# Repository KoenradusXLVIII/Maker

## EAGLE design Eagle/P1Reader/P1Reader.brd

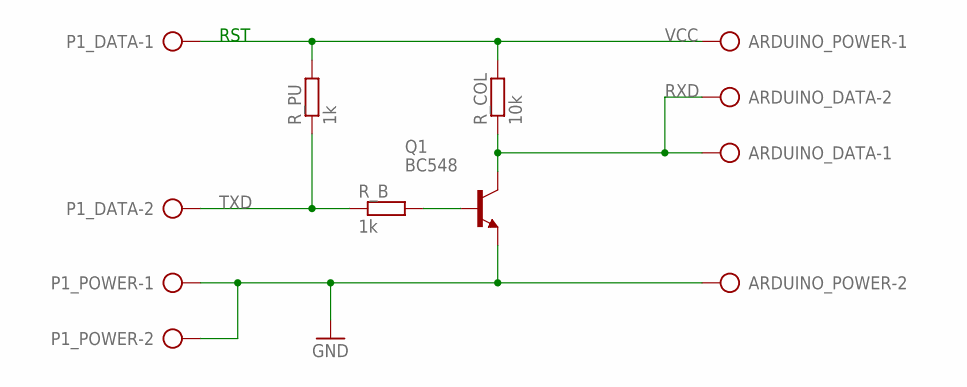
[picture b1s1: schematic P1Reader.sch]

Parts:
ARDUINO_DATA: AK500/2-H
ARDUINO_POWER: AK500/2-H
P1_DATA, P1_POWER: AK500/2-H
Q1: BC548; TO92-EBC
R_B: 1k; 0207/7
R_COL: 10k; 0207/7
R_PU: 1k; 0207/7

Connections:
GND: ARDUINO_POWER.2, P1_POWER.1, P1_POWER.2, Q1.E
unnamed: Q1.B, R_B.2
RXD: ARDUINO_DATA.1, ARDUINO_DATA.2, Q1.C, R_COL.1
TXD: P1_DATA.2, R_B.1, R_PU.1
VCC: ARDUINO_POWER.1, P1_DATA.1, R_COL.2, R_PU.2

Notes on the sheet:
RST

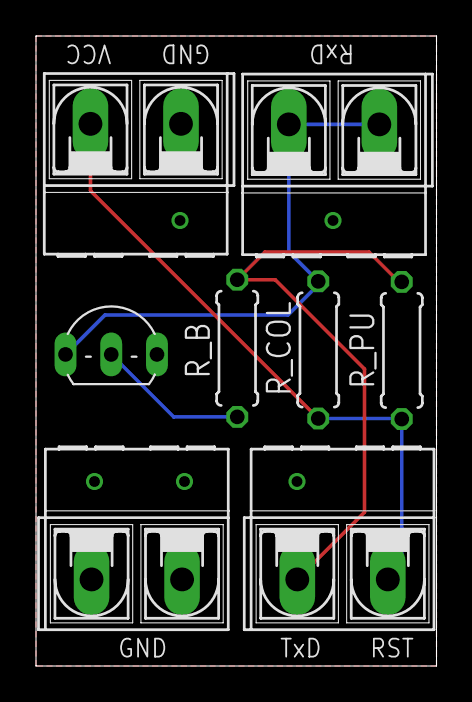
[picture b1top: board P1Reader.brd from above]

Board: 2 copper layers, 22.2 x 35.0 mm, 8 parts (0 on the bottom side), 5 nets.

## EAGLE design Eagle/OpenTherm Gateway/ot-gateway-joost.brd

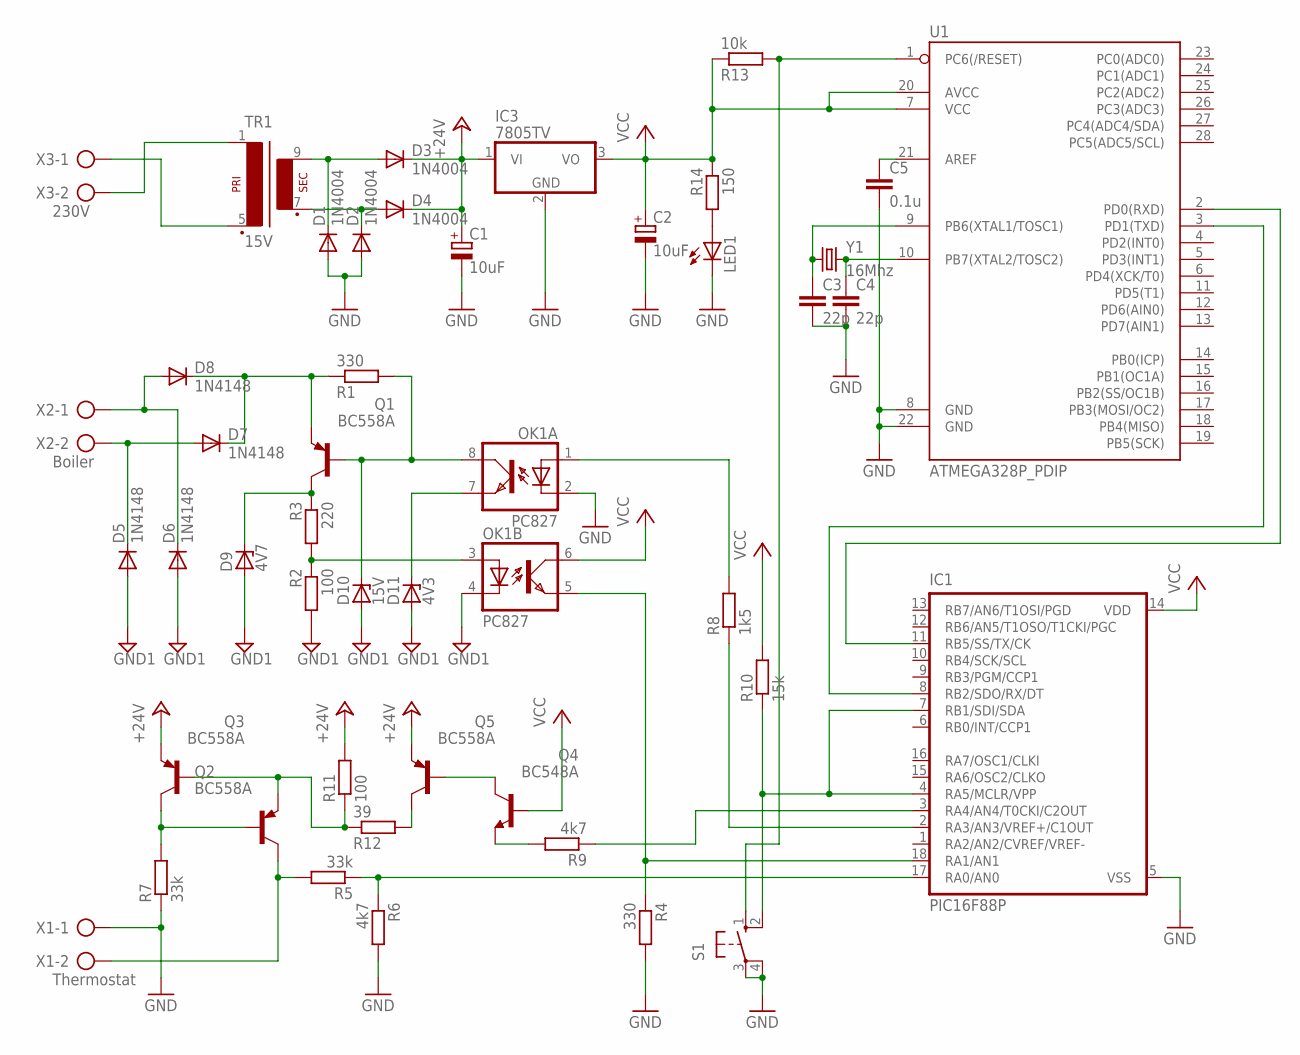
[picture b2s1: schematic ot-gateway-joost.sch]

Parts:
C1, C2: 10uF; E2,5-6
C3, C4: 22p; C025-024X044
C5: 0.1u; C025-024X044
D1, D2, D3, D4: 1N4004; DO41-10
D5, D6, D7, D8: 1N4148; DO35-10
D9: 4V7; DO41Z10
D10: 15V; DO41Z10
D11: 4V3; DO41Z10
IC1: PIC16F88P; DIL18
IC3: 7805TV; TO220V
LED1: LED3MM
OK1: PC827; DIL08
Q1, Q2, Q3, Q5: BC558A; TO92-EBC
Q4: BC548A; TO92-EBC
R1, R4: 330; 0204/7
R2, R11: 100; 0204/7
R3: 220; 0204/7
R5, R7: 33k; 0204/7
R6, R9: 4k7; 0204/7
R8: 1k5; 0204/7
R10: 15k; 0204/7
R12: 39; 0204/7
R13: 10k; 0204/7
R14: 150; 0204/7
S1: 10-XX; B3F-10XX
TR1: 15V; EI30-1
U1: ATMEGA328P_PDIP; DIL28-3
X1: Thermostat; AK500/2
X2: Boiler; AK500/2
X3: 230V; AK500/2
Y1: 16Mhz; HC49US

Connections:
+24V: C1.+, D3.C, D4.C, IC3.1 (VI), Q3.E, Q5.E, R11.2
GND: C1.-, C2.-, C3.2, C4.2, C5.2, D1.A, D2.A, IC1.5 (VSS), IC3.2 (GND), LED1.K (C), OK1.2 (C), R4.2, R6.2, R7.1, S1.3, S1.4 (P1), U1.8 (GND), U1.22 (GND), X1.1
GND1: D5.A, D6.A, D9.A, D10.A, D11.A, OK1.4 (C), R2.2
unnamed: D7.C, D8.C, Q1.E, R1.1
unnamed: Q2.B, Q3.C, R7.2
unnamed: Q2.C, R5.2, X1.2
unnamed: Q2.E, Q3.B, R11.1, R12.1
unnamed: OK1.3 (A), R2.1, R3.2
unnamed: IC1.3 (RA4/AN4/T0CKI/C2OUT), R9.1
unnamed: Q4.C, Q5.B
unnamed: D9.C, Q1.C, R3.1
unnamed: IC1.8 (RB2/SDO/RX/DT), U1.3 (PD1(TXD))
unnamed: D10.C, OK1.8 (COL), Q1.B, R1.2
unnamed: Q5.C, R12.2
unnamed: IC1.2 (RA3/AN3/VREF+/C1OUT), R8.1
unnamed: IC1.17 (RA0/AN0), R5.1, R6.1
unnamed: IC1.11 (RB5/SS/TX/CK), U1.2 (PD0(RXD))
unnamed: R13.2, S1.1 (S), U1.1 (PC6(/RESET))
unnamed: LED1.A, R14.2
unnamed: C3.1, U1.9 (PB6(XTAL1/TOSC1)), Y1.1
unnamed: C4.1, U1.10 (PB7(XTAL2/TOSC2)), Y1.2
unnamed: C5.1, U1.21 (AREF)
unnamed: D5.C, D7.A, X2.2
unnamed: D6.C, D8.A, X2.1
unnamed: D2.C, D4.A, TR1.7 (S3)
unnamed: D1.C, D3.A, TR1.9 (S4)
unnamed: TR1.5 (P2), X3.1
unnamed: IC1.18 (RA1/AN1), OK1.5 (EMIT), R4.1
unnamed: D11.C, OK1.7 (EMIT)
unnamed: IC1.4 (RA5/MCLR/VPP), IC1.7 (RB1/SDI/SDA), R10.1, S1.2 (S1)
unnamed: TR1.1, X3.2
unnamed: Q4.E, R9.2
unnamed: OK1.1 (A), R8.2
VCC: C2.+, IC1.14 (VDD), IC3.3 (VO), OK1.6 (COL), Q4.B, R10.2, R13.1, R14.1, U1.7 (VCC), U1.20 (AVCC)

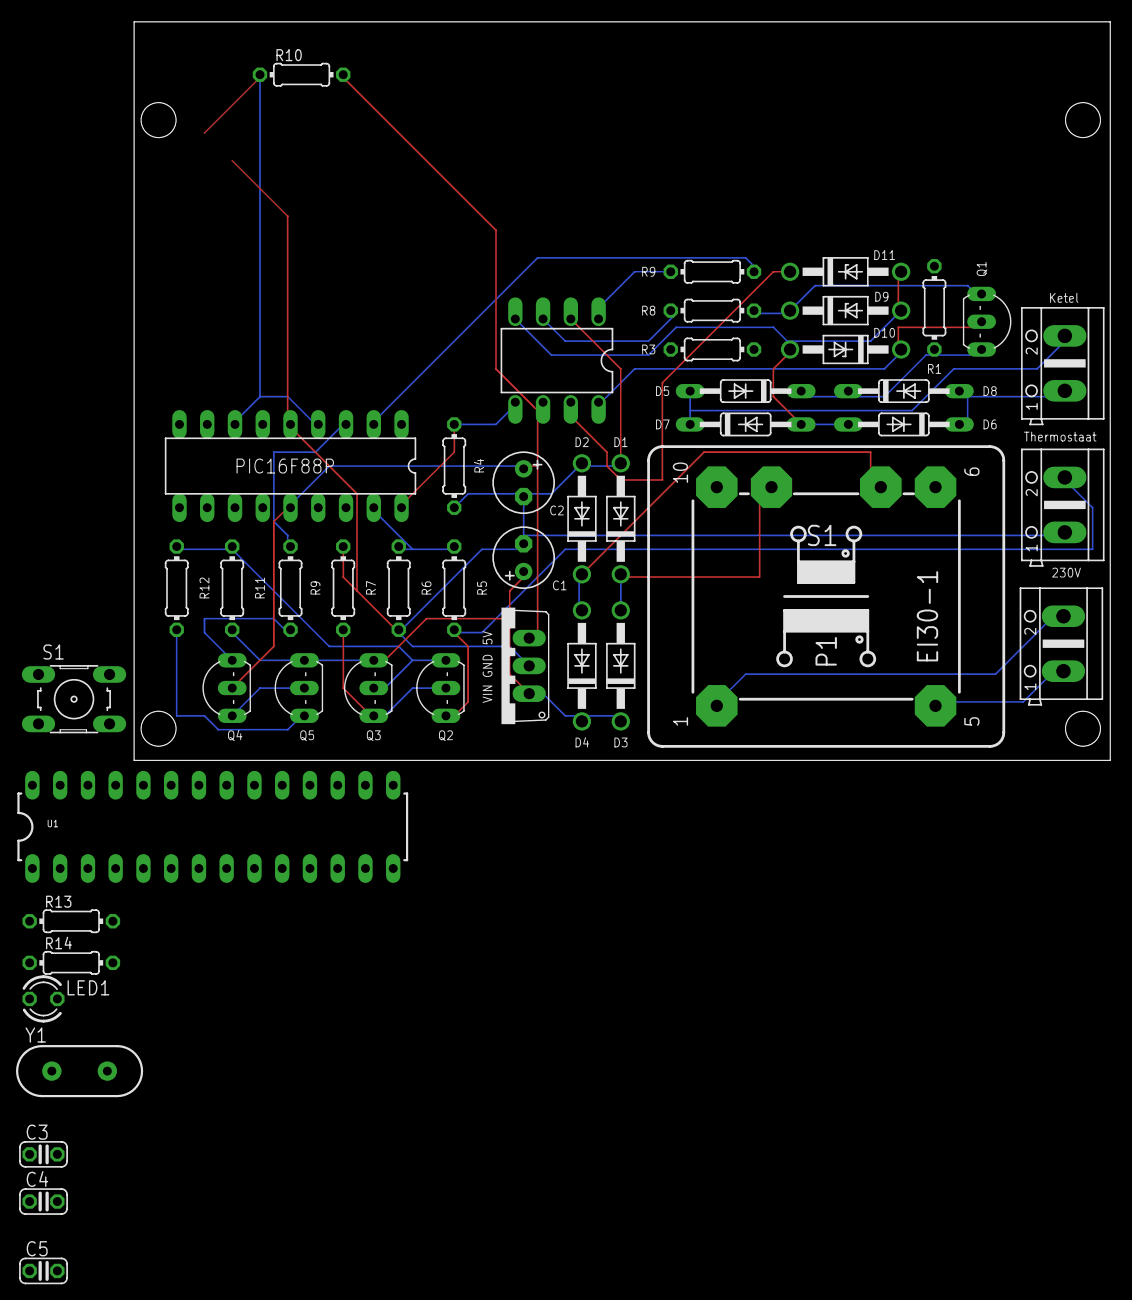
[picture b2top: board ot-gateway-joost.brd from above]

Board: 2 copper layers, 89.3 x 67.6 mm, 46 parts (0 on the bottom side), 34 nets.

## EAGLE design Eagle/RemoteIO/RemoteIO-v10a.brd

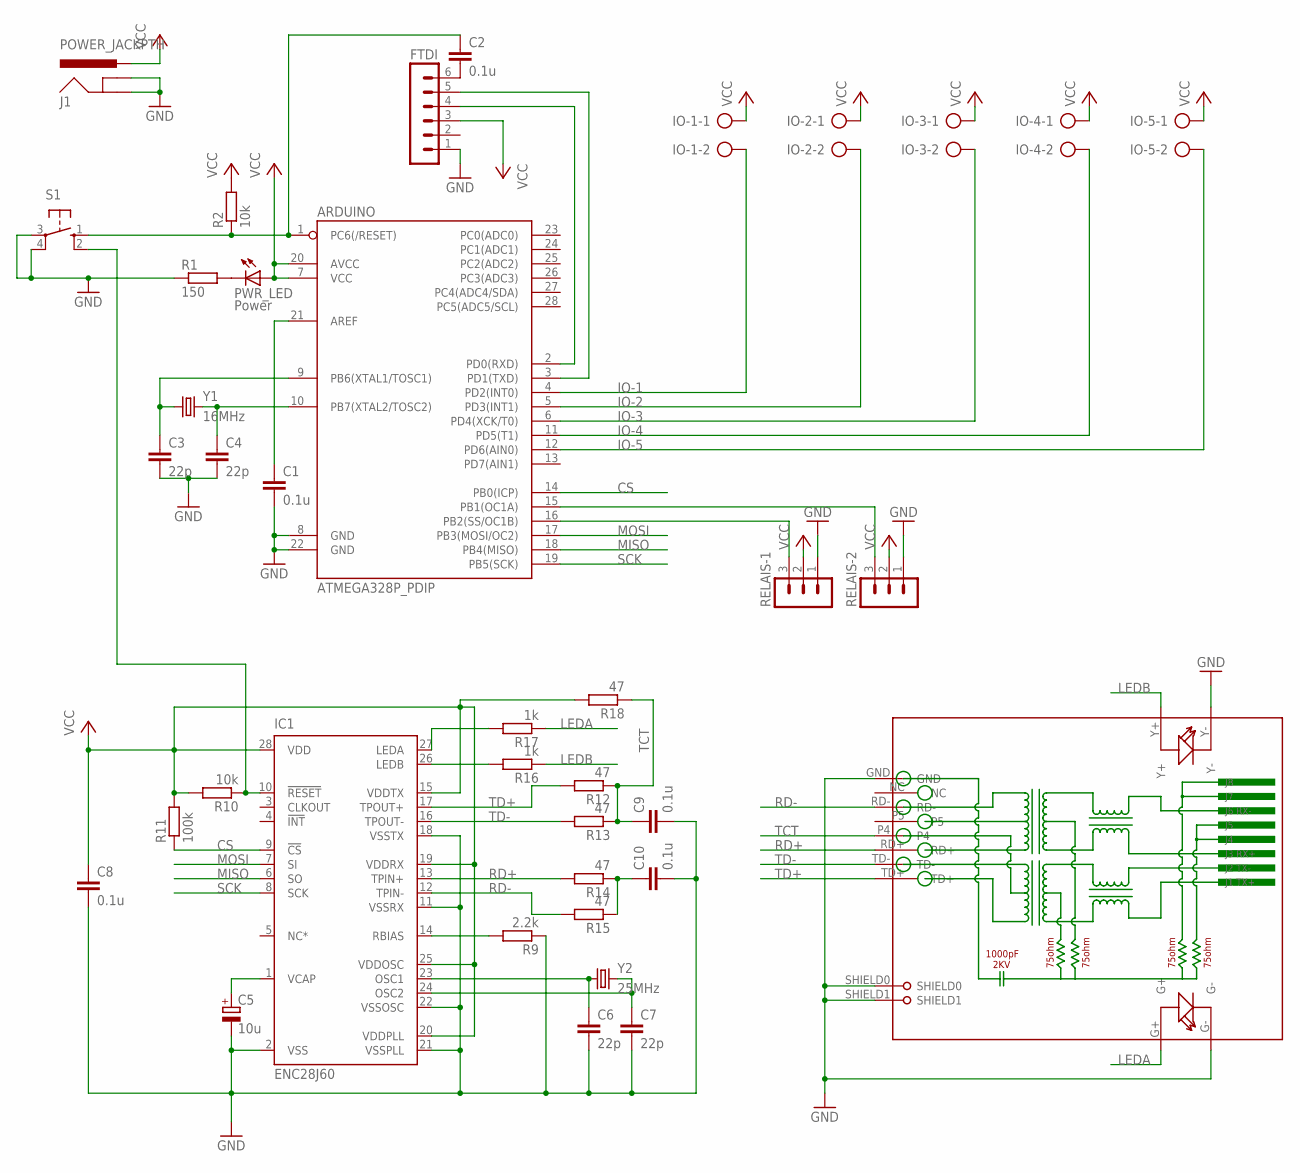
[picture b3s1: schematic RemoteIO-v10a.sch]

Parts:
ARDUINO: ATMEGA328P_PDIP; DIL28-3
C1, C2, C8, C9, C10: 0.1u; C025-024X044
C3, C4, C6, C7: 22p; C025-024X044
C5: 10u; E2,5-6
FTDI: MA06-1
IC1: ENC28J60; DIL28-3
IO-1, IO-2, IO-3, IO-4, IO-5: AK500/2
J1: POWER_JACKPTH; POWER_JACK_PTH
PWR_LED: Power; LED3MM
R1: 150; 0207/7
R2, R10: 10k; 0207/7
R9: 2.2k; 0207/7
R11: 100k; 0207/7
R12, R13, R14, R15, R18: 47; 0207/7
R16, R17: 1k; 0207/7
RELAIS-1, RELAIS-2: MA03-1
RJ1: HR911105A
S1: 10-XX; B3F-10XX
Y1: 16MHz; HC49US
Y2: 25MHz; HC49US

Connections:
CS: ARDUINO.14 (PB0(ICP)), IC1.9 (!CS), R11.1
GND: ARDUINO.8 (GND), ARDUINO.22 (GND), C1.2, C3.2, C4.2, C5.-, C6.2, C7.2, C8.2, C9.2, C10.2, FTDI.1, IC1.2 (VSS), IC1.11 (VSSRX), IC1.18 (VSSTX), IC1.21 (VSSPLL), IC1.22 (VSSOSC), J1.GND, J1.GNDBREAK, R1.1, R9.1, RELAIS-1.1, RELAIS-2.1, RJ1.G-, RJ1.GND, RJ1.SHIELD0, RJ1.SHIELD1, RJ1.Y-, S1.3, S1.4 (P1)
IO-1: ARDUINO.4 (PD2(INT0)), IO-1.2
IO-2: ARDUINO.5 (PD3(INT1)), IO-2.2
IO-3: ARDUINO.6 (PD4(XCK/T0)), IO-3.2
IO-4: ARDUINO.11 (PD5(T1)), IO-4.2
IO-5: ARDUINO.12 (PD6(AIN0)), IO-5.2
LEDA: R17.1, RJ1.G+
LEDB: R16.1, RJ1.Y+
MISO: ARDUINO.18 (PB4(MISO)), IC1.6 (SO)
MOSI: ARDUINO.17 (PB3(MOSI/OC2)), IC1.7 (SI)
unnamed: ARDUINO.1 (PC6(/RESET)), C2.1, R2.1, S1.1 (S)
unnamed: ARDUINO.9 (PB6(XTAL1/TOSC1)), C3.1, Y1.1
unnamed: ARDUINO.10 (PB7(XTAL2/TOSC2)), C4.1, Y1.2
unnamed: ARDUINO.21 (AREF), C1.1
unnamed: PWR_LED.K (C), R1.2
unnamed: IC1.14 (RBIAS), R9.2
unnamed: ARDUINO.16 (PB2(SS/OC1B)), RELAIS-1.3
unnamed: C2.2, FTDI.6
unnamed: ARDUINO.3 (PD1(TXD)), FTDI.5
unnamed: ARDUINO.2 (PD0(RXD)), FTDI.4
unnamed: C6.1, IC1.23 (OSC1), Y2.1
unnamed: IC1.26 (LEDB), R16.2
unnamed: ARDUINO.15 (PB1(OC1A)), RELAIS-2.3
unnamed: C5.+, IC1.1 (VCAP)
unnamed: C7.1, IC1.24 (OSC2), Y2.2
unnamed: C10.1, R14.1, R15.1
unnamed: IC1.27 (LEDA), R17.2
unnamed: IC1.10 (!RESET), R10.1, S1.2 (S1)
RD+: IC1.13 (TPIN+), R14.2, RJ1.RD+
RD-: IC1.12 (TPIN-), R15.2, RJ1.RD-
SCK: ARDUINO.19 (PB5(SCK)), IC1.8 (SCK)
TCT: C9.1, R12.1, R13.1, R18.1, RJ1.P4
TD+: IC1.17 (TPOUT+), R12.2, RJ1.TD+
TD-: IC1.16 (TPOUT-), R13.2, RJ1.TD-
VCC: ARDUINO.7 (VCC), ARDUINO.20 (AVCC), C8.1, FTDI.3, IC1.15 (VDDTX), IC1.19 (VDDRX), IC1.20 (VDDPLL), IC1.25 (VDDOSC), IC1.28 (VDD), IO-1.1, IO-2.1, IO-3.1, IO-4.1, IO-5.1, J1.PWR, PWR_LED.A, R2.2, R10.2, R11.2, R18.2, RELAIS-1.2, RELAIS-2.2

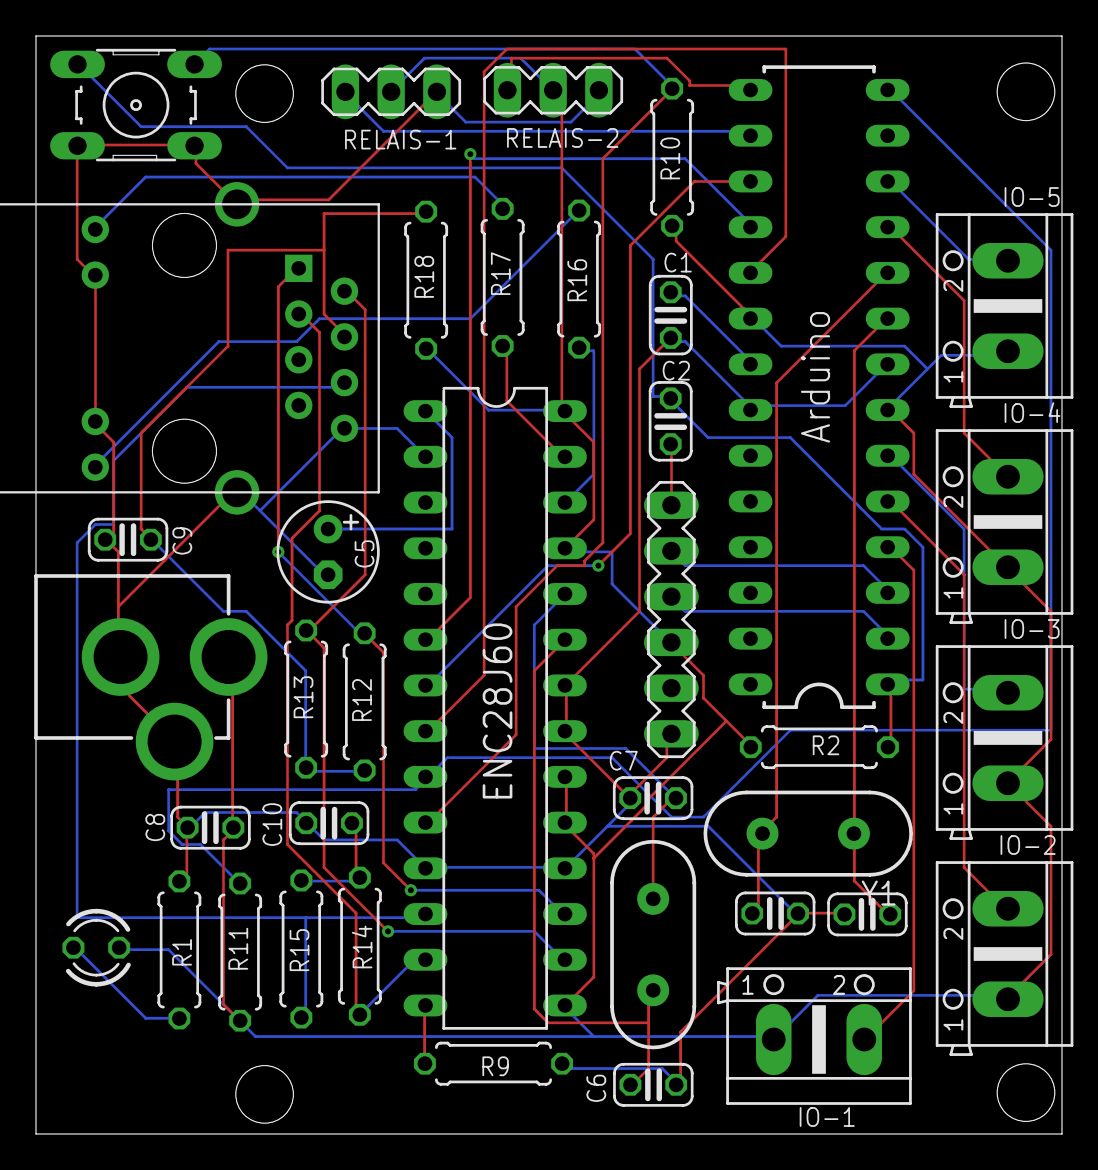
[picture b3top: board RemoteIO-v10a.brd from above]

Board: 2 copper layers, 57.0 x 61.0 mm, 38 parts (0 on the bottom side), 36 nets.

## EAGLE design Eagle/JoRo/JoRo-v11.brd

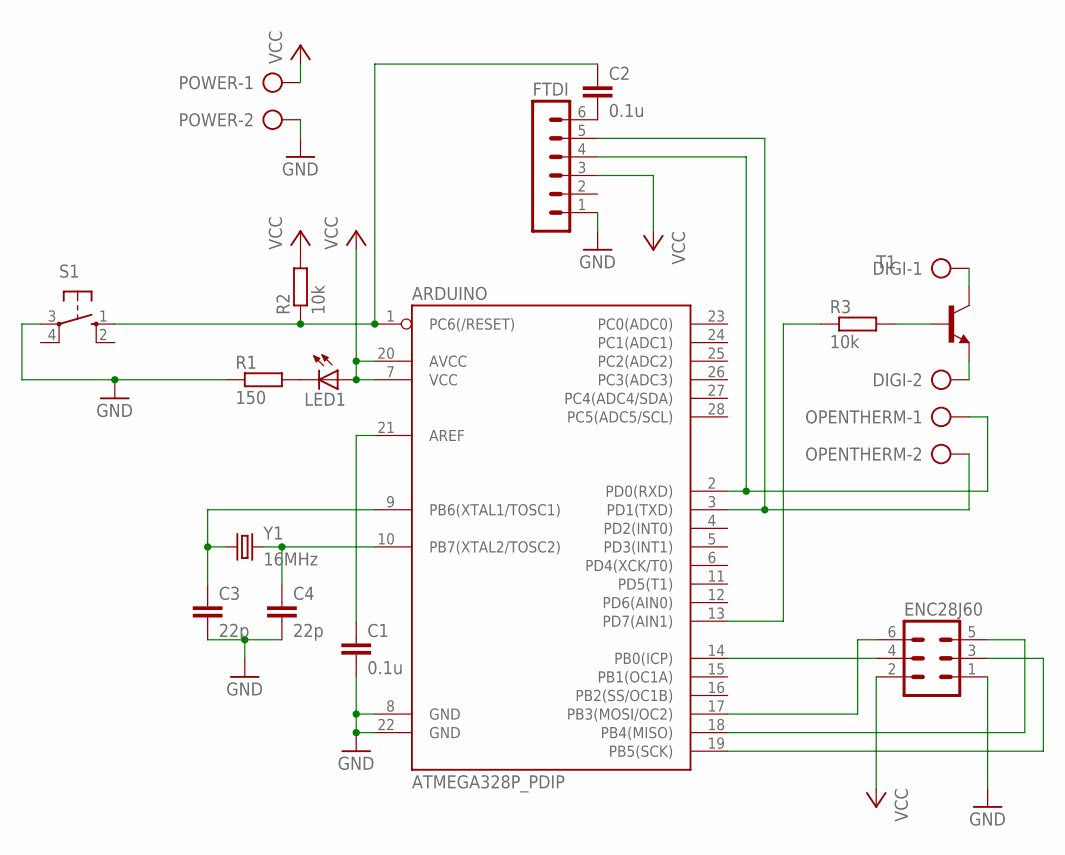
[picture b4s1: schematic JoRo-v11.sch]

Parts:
ARDUINO: ATMEGA328P_PDIP; DIL28-3
C1, C2: 0.1u; C025-024X044
C3, C4: 22p; C025-024X044
DIGI: AK500/2
ENC28J60: MA03-2
FTDI: MA06-1
LED1: LED3MM
OPENTHERM: AK500/2
POWER: AK500/2
R1: 150; 0207/7
R2, R3: 10k; 0207/7
S1: 10-XX; B3F-10XX
T1: BC548-NPN-TO92-CBE; TO92-CBE
Y1: 16MHz; HC49US

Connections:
GND: ARDUINO.8 (GND), ARDUINO.22 (GND), C1.2, C3.2, C4.2, ENC28J60.1, FTDI.1, POWER.2, R1.1, S1.3
unnamed: ARDUINO.1 (PC6(/RESET)), C2.1, R2.1, S1.1 (S)
unnamed: ARDUINO.9 (PB6(XTAL1/TOSC1)), C3.1, Y1.1
unnamed: ARDUINO.10 (PB7(XTAL2/TOSC2)), C4.1, Y1.2
unnamed: ARDUINO.21 (AREF), C1.1
unnamed: LED1.K (C), R1.2
unnamed: ARDUINO.19 (PB5(SCK)), ENC28J60.3
unnamed: C2.2, FTDI.6
unnamed: ARDUINO.3 (PD1(TXD)), FTDI.5, OPENTHERM.2
unnamed: ARDUINO.2 (PD0(RXD)), FTDI.4, OPENTHERM.1
unnamed: ARDUINO.14 (PB0(ICP)), ENC28J60.4
unnamed: ARDUINO.17 (PB3(MOSI/OC2)), ENC28J60.6
unnamed: ARDUINO.18 (PB4(MISO)), ENC28J60.5
unnamed: R3.2, T1.B
unnamed: ARDUINO.13 (PD7(AIN1)), R3.1
unnamed: DIGI.1, T1.C
unnamed: DIGI.2, T1.E
VCC: ARDUINO.7 (VCC), ARDUINO.20 (AVCC), ENC28J60.2, FTDI.3, LED1.A, POWER.1, R2.2

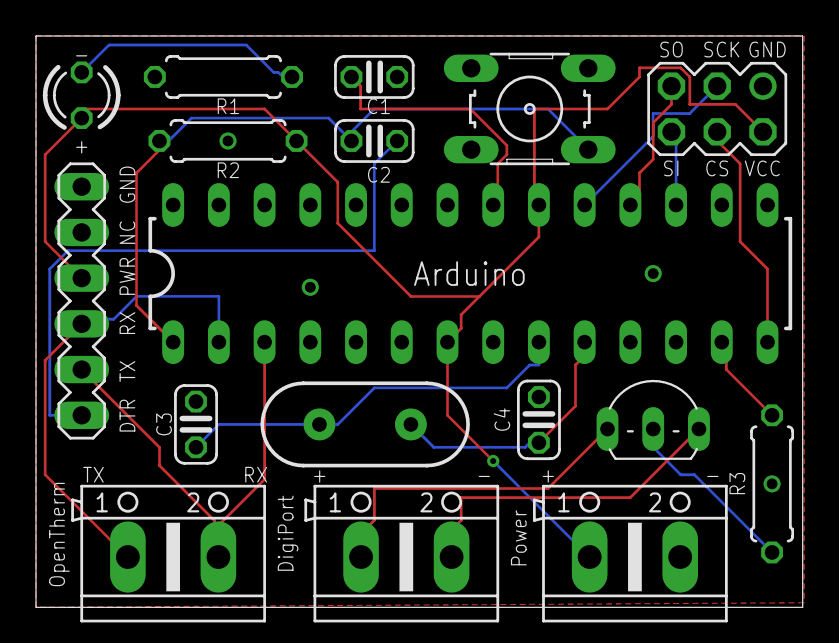
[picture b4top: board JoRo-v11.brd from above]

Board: 2 copper layers, 42.6 x 31.7 mm, 17 parts (0 on the bottom side), 18 nets.

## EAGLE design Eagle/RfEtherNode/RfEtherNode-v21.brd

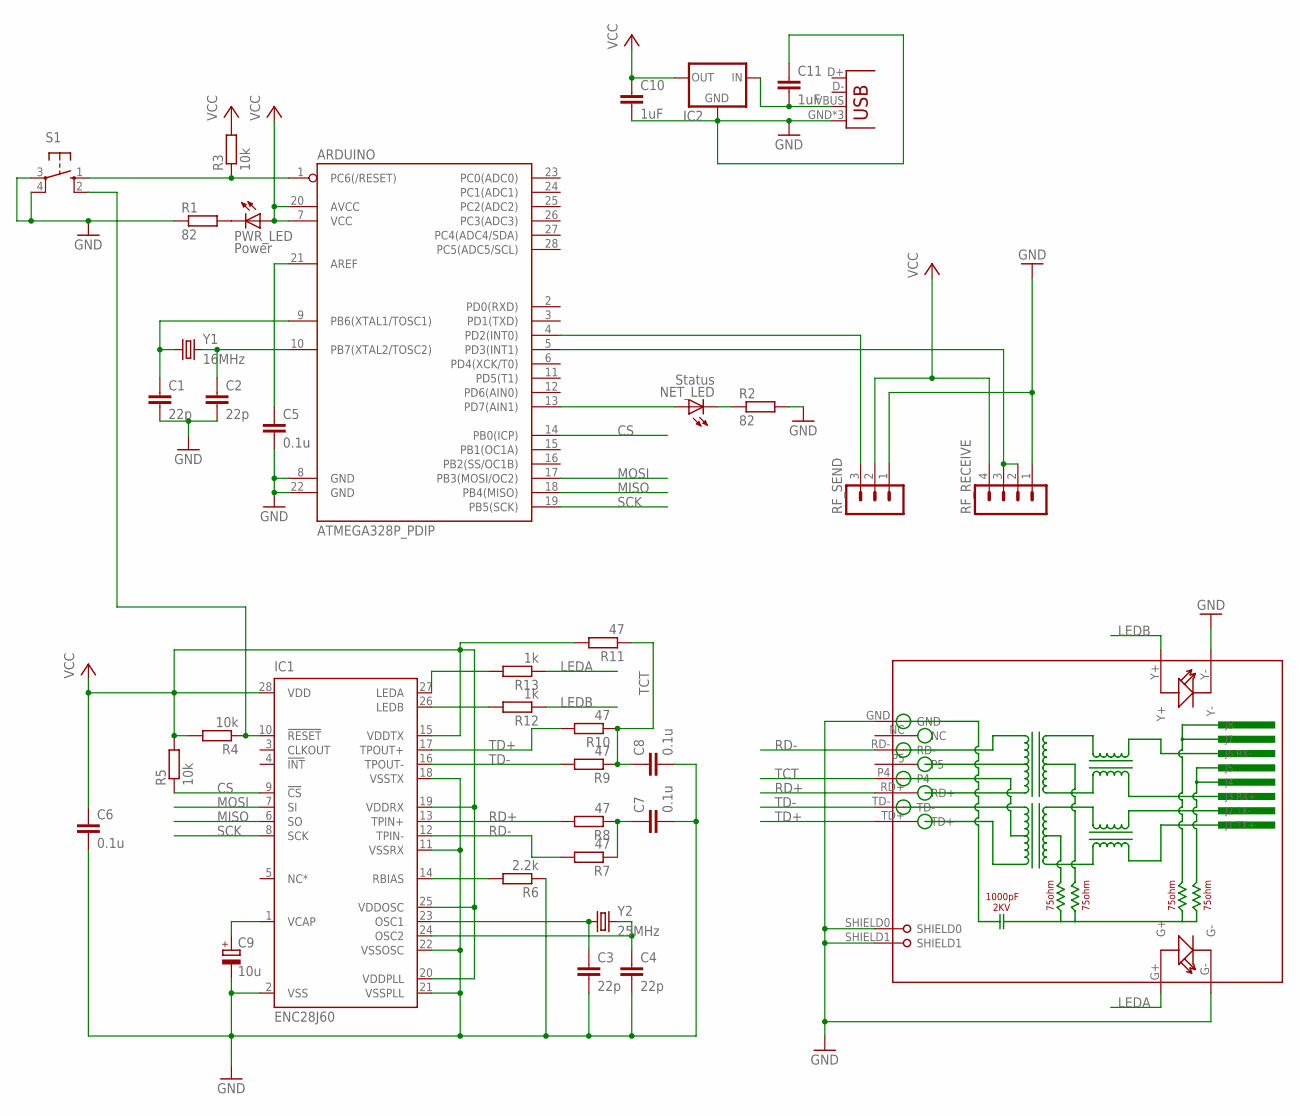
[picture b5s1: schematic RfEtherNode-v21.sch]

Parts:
ARDUINO: ATMEGA328P_PDIP; DIL28-3
C1, C2, C3, C4: 22p; C025-024X044
C5, C6, C7, C8: 0.1u; C025-024X044
C9: 10u; E2,5-6
C10, C11: 1uF; C025-024X044
IC1: ENC28J60; DIL28-3
IC2: V_REG_78XXTO-92_UNTESTED; TO-92
JP1: USB-MICROB
NET_LED: Status; LED3MM
PWR_LED: Power; LED3MM
R1, R2: 82; 0207/7
R3, R4, R5: 10k; 0207/7
R6: 2.2k; 0207/7
R7, R8, R9, R10, R11: 47; 0207/7
R12, R13: 1k; 0207/7
RF_RECEIVE: MA04-1
RF_SEND: MA03-1
RJ1: HR911105A
S1: 10-XX; B3F-10XX
Y1: 16MHz; HC49US
Y2: 25MHz; HC49US

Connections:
CS: ARDUINO.14 (PB0(ICP)), IC1.9 (!CS), R5.1
GND: ARDUINO.8 (GND), ARDUINO.22 (GND), C1.2, C2.2, C3.2, C4.2, C5.2, C6.2, C7.2, C8.2, C9.-, C10.2, C11.1, IC1.2 (VSS), IC1.11 (VSSRX), IC1.18 (VSSTX), IC1.21 (VSSPLL), IC1.22 (VSSOSC), IC2.1 (GND), JP1.GND, JP1.MT1 (GND), JP1.MT2 (GND), R1.1, R2.2, R6.1, RF_RECEIVE.1, RF_SEND.1, RJ1.G-, RJ1.GND, RJ1.SHIELD0, RJ1.SHIELD1, RJ1.Y-, S1.3, S1.4 (P1)
LEDA: R13.1, RJ1.G+
LEDB: R12.1, RJ1.Y+
MISO: ARDUINO.18 (PB4(MISO)), IC1.6 (SO)
MOSI: ARDUINO.17 (PB3(MOSI/OC2)), IC1.7 (SI)
unnamed: ARDUINO.1 (PC6(/RESET)), R3.1, S1.1 (S)
unnamed: ARDUINO.9 (PB6(XTAL1/TOSC1)), C1.1, Y1.1
unnamed: ARDUINO.10 (PB7(XTAL2/TOSC2)), C2.1, Y1.2
unnamed: ARDUINO.21 (AREF), C5.1
unnamed: PWR_LED.K (C), R1.2
unnamed: IC1.14 (RBIAS), R6.2
unnamed: ARDUINO.4 (PD2(INT0)), RF_SEND.3
unnamed: C11.2, IC2.2 (IN), JP1.VBUS
unnamed: ARDUINO.5 (PD3(INT1)), RF_RECEIVE.2, RF_RECEIVE.3
unnamed: C3.1, IC1.23 (OSC1), Y2.1
unnamed: IC1.26 (LEDB), R12.2
unnamed: C9.+, IC1.1 (VCAP)
unnamed: C4.1, IC1.24 (OSC2), Y2.2
unnamed: C7.1, R7.1, R8.1
unnamed: IC1.27 (LEDA), R13.2
unnamed: ARDUINO.13 (PD7(AIN1)), NET_LED.A
unnamed: IC1.10 (!RESET), R4.1, S1.2 (S1)
unnamed: NET_LED.K (C), R2.1
RD+: IC1.13 (TPIN+), R8.2, RJ1.RD+
RD-: IC1.12 (TPIN-), R7.2, RJ1.RD-
SCK: ARDUINO.19 (PB5(SCK)), IC1.8 (SCK)
TCT: C8.1, R9.1, R10.1, R11.1, RJ1.P4
TD+: IC1.17 (TPOUT+), R10.2, RJ1.TD+
TD-: IC1.16 (TPOUT-), R9.2, RJ1.TD-
VCC: ARDUINO.7 (VCC), ARDUINO.20 (AVCC), C6.1, C10.1, IC1.15 (VDDTX), IC1.19 (VDDRX), IC1.20 (VDDPLL), IC1.25 (VDDOSC), IC1.28 (VDD), IC2.3 (OUT), PWR_LED.A, R3.2, R4.2, R5.2, R11.2, RF_RECEIVE.4, RF_SEND.2

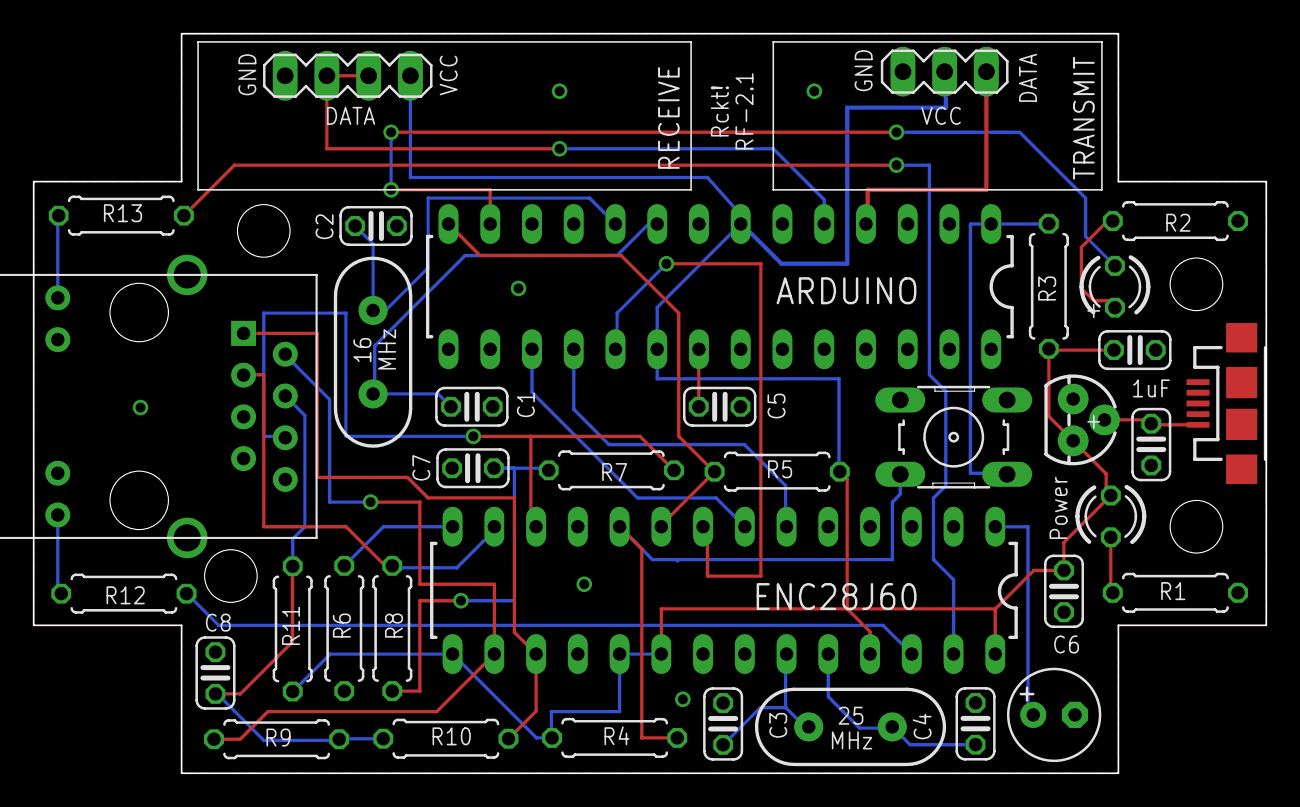
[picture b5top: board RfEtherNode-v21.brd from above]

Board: 2 copper layers, 75.0 x 45.0 mm, 36 parts (0 on the bottom side), 31 nets.

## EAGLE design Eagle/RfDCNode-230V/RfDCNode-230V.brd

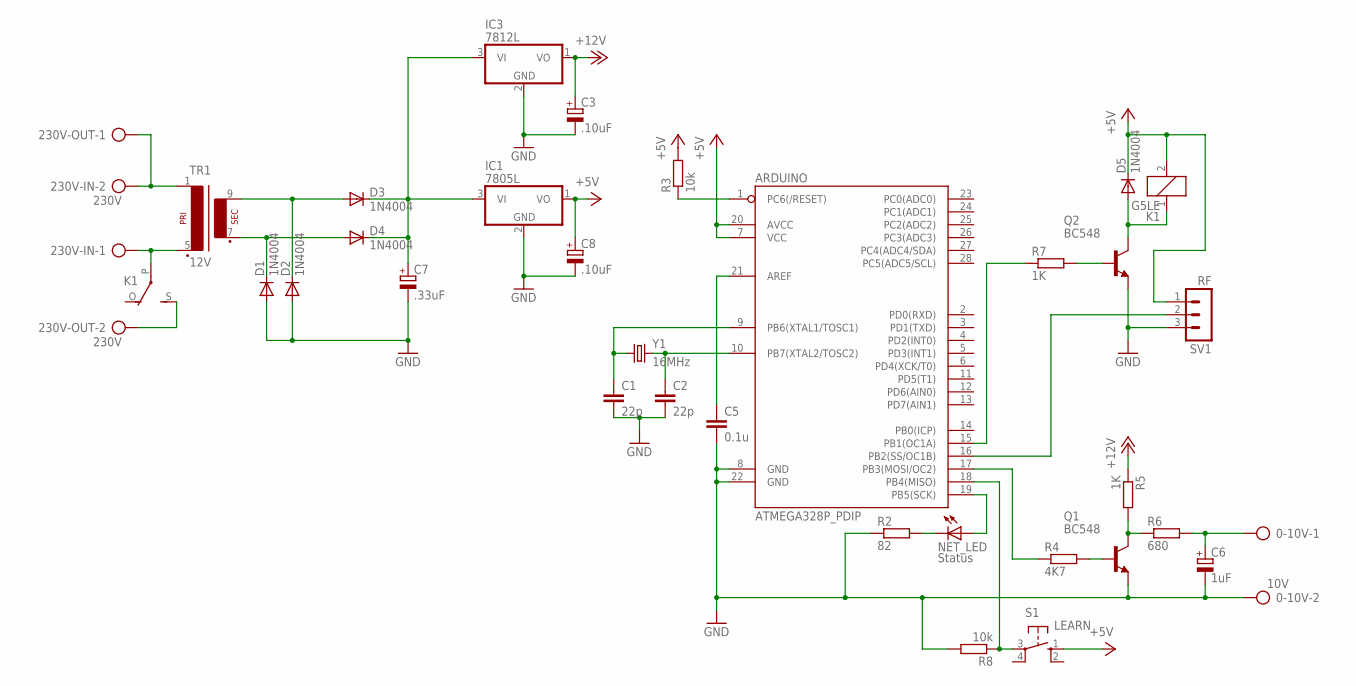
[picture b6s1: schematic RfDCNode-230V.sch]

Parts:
0-10V: 10V; AK500/2
230V-IN, 230V-OUT: 230V; AK500/2
ARDUINO: ATMEGA328P_PDIP; DIL28-3
C1, C2: 22p; C025-024X044
C3, C8: .10uF; E1,8-4
C5: 0.1u; C025-024X044
C6: 1uF; E2,5-6
C7: .33uF; E1,8-4
D1, D2, D3, D4, D5: 1N4004; DO41-10
IC1: 7805L; TO92
IC3: 7812L; TO92
K1: G5LE
NET_LED: Status; LED3MM
Q1, Q2: BC548; TO92-EBC
R2: 82; 0207/7
R3, R8: 10k; 0207/7
R4: 4K7; 0207/7
R5, R7: 1K; 0207/7
R6: 680; 0207/7
S1: LEARN; B3F-10XX
SV1: RF; MA03-1
TR1: 12V; EI30-1
Y1: 16MHz; HC49US

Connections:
+5V: ARDUINO.7 (VCC), ARDUINO.20 (AVCC), C8.+, D5.C, IC1.1 (VO), K1.2, R3.2, S1.1 (S), SV1.1
+12V: C3.+, IC3.1 (VO), R5.1
GND: 0-10V.2, ARDUINO.8 (GND), ARDUINO.22 (GND), C1.2, C2.2, C3.-, C5.2, C6.-, C7.-, C8.-, D1.A, D2.A, IC1.2 (GND), IC3.2 (GND), Q1.E, Q2.E, R2.1, R8.2, SV1.3
unnamed: ARDUINO.1 (PC6(/RESET)), R3.1
unnamed: ARDUINO.9 (PB6(XTAL1/TOSC1)), C1.1, Y1.1
unnamed: ARDUINO.10 (PB7(XTAL2/TOSC2)), C2.1, Y1.2
unnamed: ARDUINO.21 (AREF), C5.1
unnamed: 230V-IN.2, 230V-OUT.1, TR1.1
unnamed: 230V-IN.1, K1.P, TR1.5 (P2)
unnamed: ARDUINO.17 (PB3(MOSI/OC2)), R4.1
unnamed: D1.C, D4.A, TR1.7 (S3)
unnamed: D2.C, D3.A, TR1.9 (S4)
unnamed: Q1.B, R4.2
unnamed: Q1.C, R5.2, R6.1
unnamed: 0-10V.1, C6.+, R6.2
unnamed: 230V-OUT.2, K1.S
unnamed: D5.A, K1.1, Q2.C
unnamed: ARDUINO.15 (PB1(OC1A)), R7.1
unnamed: Q2.B, R7.2
unnamed: ARDUINO.18 (PB4(MISO)), R8.1, S1.3
unnamed: ARDUINO.16 (PB2(SS/OC1B)), SV1.2
unnamed: NET_LED.K (C), R2.2
unnamed: ARDUINO.19 (PB5(SCK)), NET_LED.A
unnamed: C7.+, D3.C, D4.C, IC1.3 (VI), IC3.3 (VI)

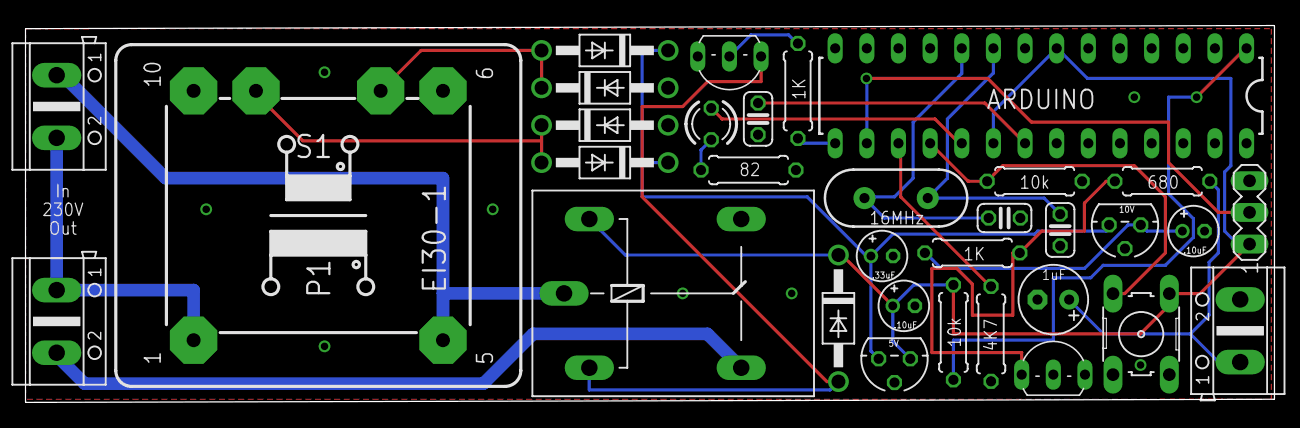
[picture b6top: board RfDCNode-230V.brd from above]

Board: 2 copper layers, 100.2 x 30.2 mm, 33 parts (0 on the bottom side), 24 nets.

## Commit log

2016-11-20 - Imported old Eagle projects - P1Reader project
2016-12-08 Initial commit of DropBoxPlus project
2017-06-04 First commit of Android app
2017-07-13 Drawing of craftsbench in shed
2019-05-19 iTemp SketchUp
2019-06-11 Initial commit of Nixie project
2019-11-24 SensorNode boxes

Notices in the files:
parts and their libraries:
SparkFun-DigitalIC: Licensing: CC v3.0 Share-Alike You are welcome to use this library for commercial purposes.
SparkFun-PowerIC: Licensing: Creative Commons ShareAlike 4.0 International - https://creativecommons.org/licenses/by-sa/4.0
